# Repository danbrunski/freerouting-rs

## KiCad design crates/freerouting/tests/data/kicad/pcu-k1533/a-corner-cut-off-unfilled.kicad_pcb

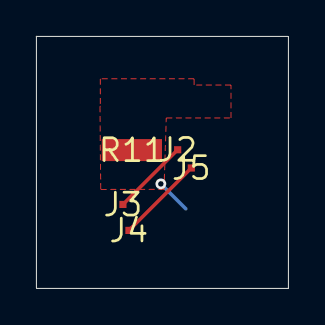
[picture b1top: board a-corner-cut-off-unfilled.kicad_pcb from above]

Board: 4 copper layers, 14.0 x 14.0 mm, 6 parts (1 on the bottom side), 3 nets.

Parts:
J1, J2, J3, J4, J5: x; smd
R11: x; smd

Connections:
/CH5_NO: J1.1, R11.1
SCL: J2.1, J3.1
VCC_3V3: J4.1, J5.1
